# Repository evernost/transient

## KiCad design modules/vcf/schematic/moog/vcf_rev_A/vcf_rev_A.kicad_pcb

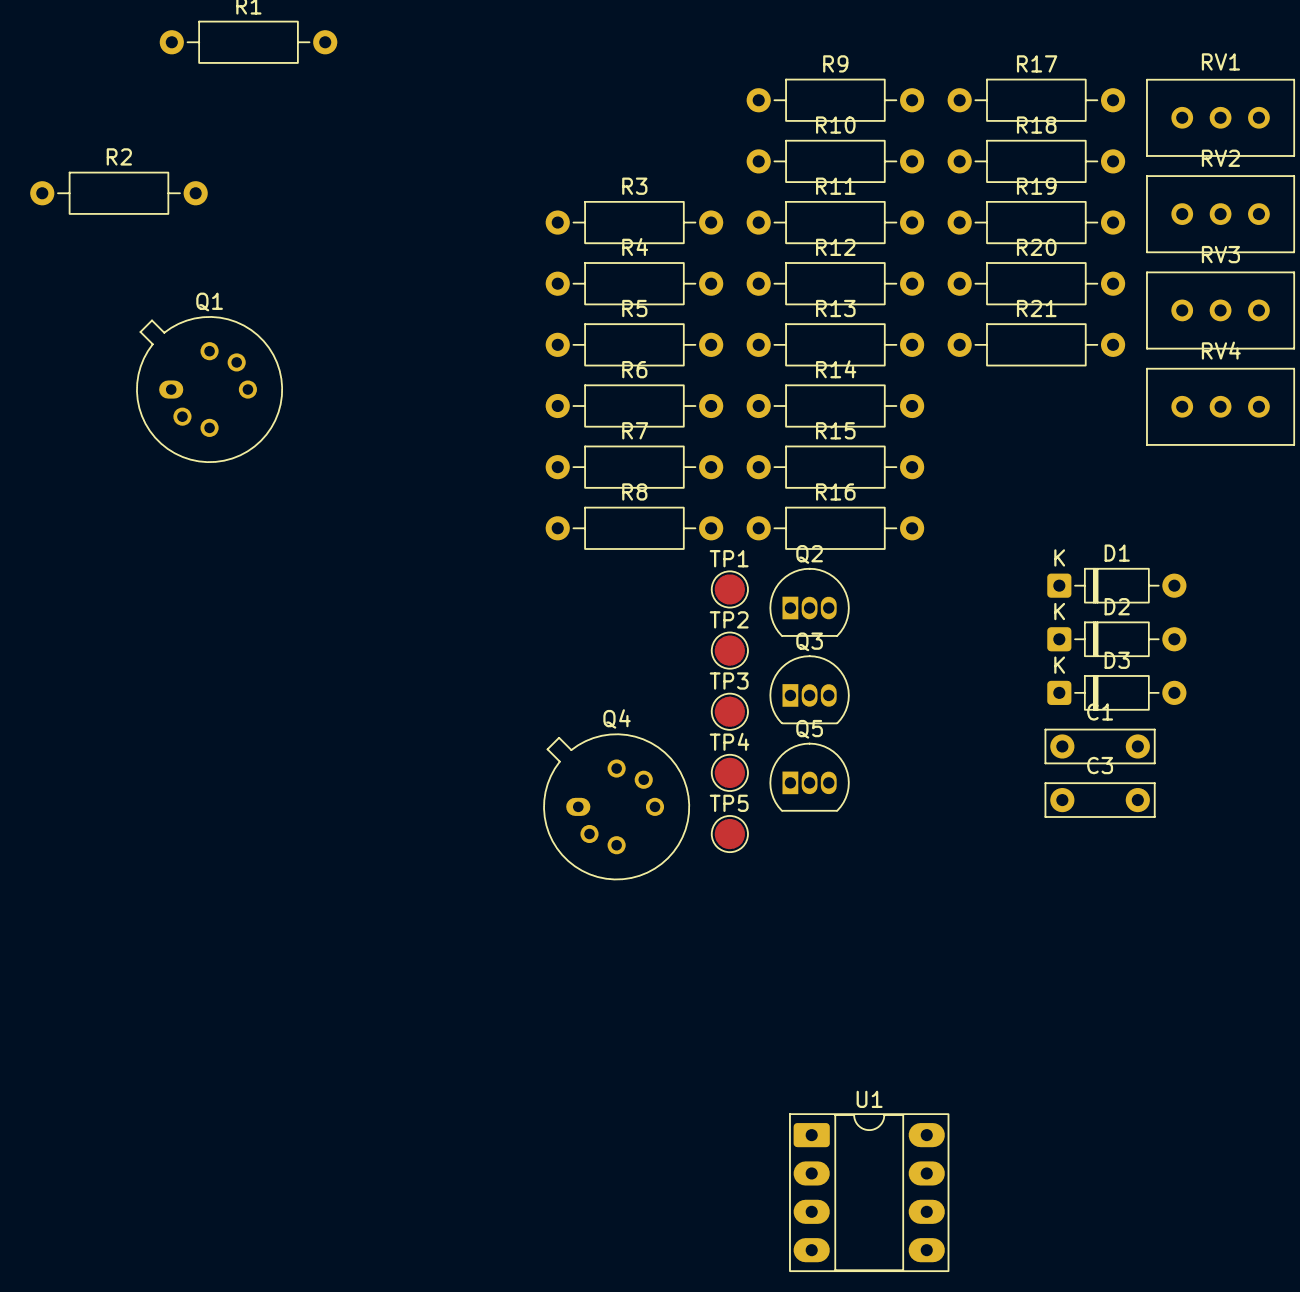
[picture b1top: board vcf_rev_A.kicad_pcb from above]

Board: 2 copper layers, 41 parts (0 on the bottom side), 31 nets, no tracks yet.

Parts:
C1: 10n; C_Rect_L7.0mm_W2.0mm_P5.00mm
C3: 100n; C_Rect_L7.0mm_W2.0mm_P5.00mm
D1, D2, D3: 1N4148; D_DO-35_SOD27_P7.62mm_Horizontal
Q1, Q4: 2N2978; TO-5-6
Q2, Q3, Q5: BC548; TO-92_Inline
R1, R2, R15, R17: 4.7; R_Axial_DIN0207_L6.3mm_D2.5mm_P10.16mm_Horizontal
R3, R4, R5, R6, R7, R14, R16, R20, R21: 10k; R_Axial_DIN0207_L6.3mm_D2.5mm_P10.16mm_Horizontal
R8, R18: 4.7k; R_Axial_DIN0207_L6.3mm_D2.5mm_P10.16mm_Horizontal
R9, R19: 220k; R_Axial_DIN0207_L6.3mm_D2.5mm_P10.16mm_Horizontal
R10, R13: 47; R_Axial_DIN0207_L6.3mm_D2.5mm_P10.16mm_Horizontal
R11, R12: 47k; R_Axial_DIN0207_L6.3mm_D2.5mm_P10.16mm_Horizontal
RV1, RV2, RV3, RV4: 500; Potentiometer_Bourns_3296W_Vertical
TP1, TP2, TP3, TP4, TP5: TestPoint; TestPoint_Pad_D2.0mm
U1: OP275; DIP-8_W7.62mm_Socket_LongPads

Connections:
+12V: C1.1, C3.1, Q3.1 (C), R3.1, R7.1, R20.1, U1.8 (V+)
-12V: C1.2, C3.2, R4.2, R21.2, U1.4 (V-)
GND: D3.1 (K), R8.2, R10.2, R13.2, R18.2, TP2.1, TP3.1, TP4.1, TP5.1
unnamed: D1.2 (A), Q3.2 (B), R7.2, TP1.1
unnamed: D1.1 (K), D2.2 (A)
unnamed: D2.1 (K), D3.2 (A)
unnamed: Q1.2 (B1), R10.1, R11.2
unnamed: Q1.3 (C1), R5.2
unnamed: Q1.1 (E1), R1.1
unnamed: Q1.6 (B2), R8.1, R9.1
unnamed: Q1.7 (C2), R6.2
unnamed: Q1.5 (E2), R2.1
unnamed: Q2.1 (C), R1.2, R2.2
unnamed: Q3.3 (E), RV2.2, RV3.2
unnamed: Q4.2 (B1), R12.2, R13.1
unnamed: Q4.3 (C1), R14.2
unnamed: Q4.1 (E1), R15.1
unnamed: Q4.6 (B2), R18.1, R19.1
unnamed: Q4.7 (C2), R16.2
unnamed: Q4.5 (E2), R17.1
unnamed: Q5.1 (C), R15.2, R17.2
unnamed: R3.2, RV1.1
unnamed: R4.1, RV1.3
unnamed: R5.1, RV2.3
unnamed: R6.1, RV2.1
unnamed: R9.2, RV1.2
unnamed: R14.1, RV3.3
unnamed: R16.1, RV3.1
unnamed: R19.2, RV4.2
unnamed: R20.2, RV4.1
unnamed: R21.1, RV4.3
